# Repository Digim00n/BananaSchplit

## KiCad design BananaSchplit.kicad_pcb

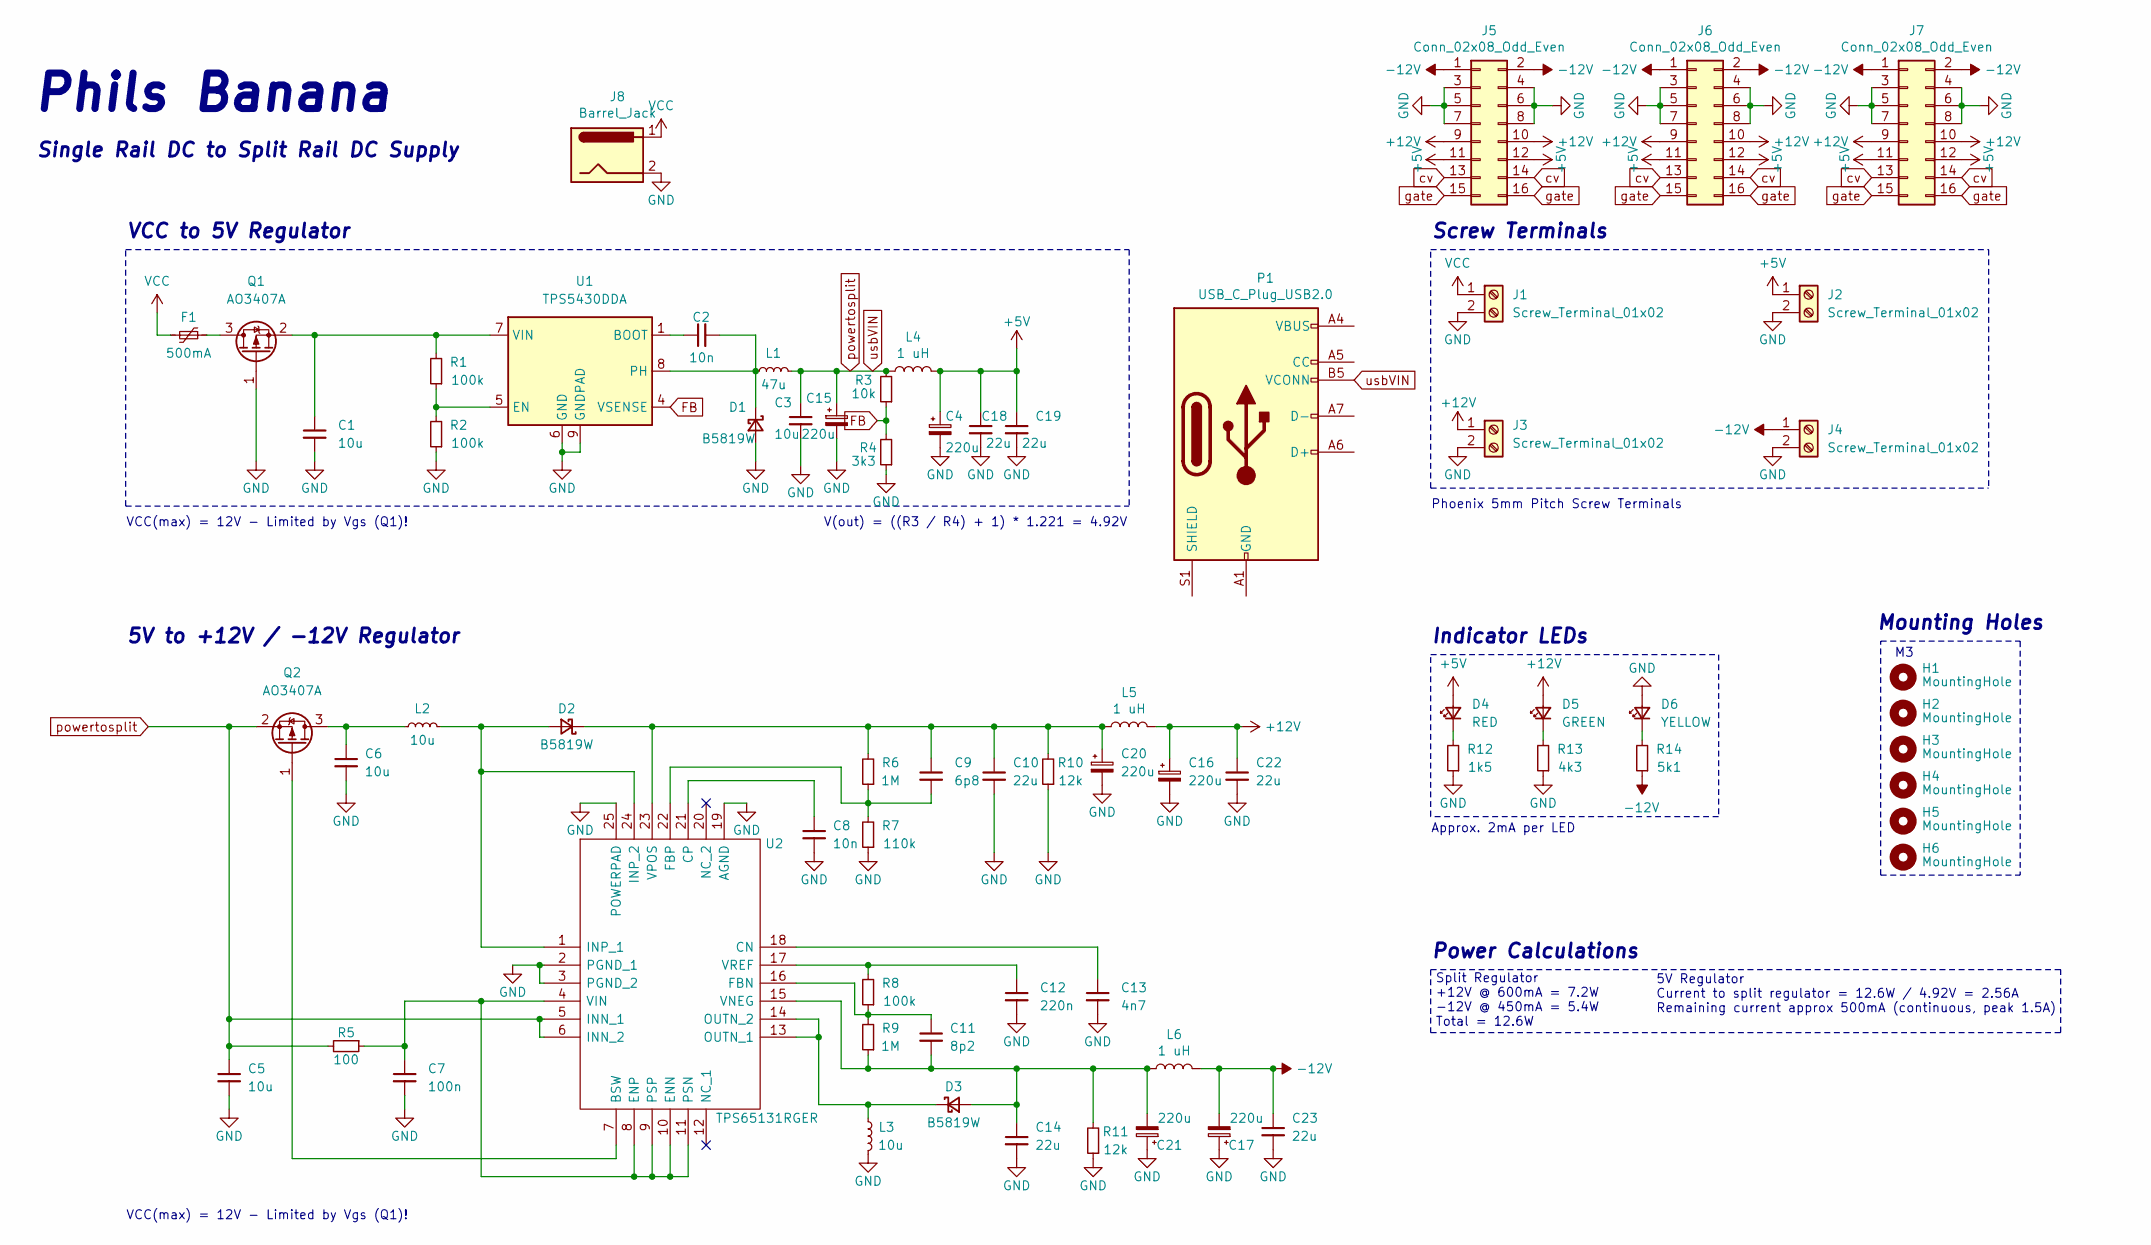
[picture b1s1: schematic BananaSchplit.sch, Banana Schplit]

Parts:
C1, C3, C5, C6: 10u; C_1206_3216Metric; LCSC Part # C13585
C2, C8: 10n; C_0603_1608Metric; LCSC Part # C57112
C4, C15, C16, C17, C20, C21: 220u; CP_Elec_6.3x7.7; LCSC Part # C127327
C7: 100n; C_0603_1608Metric; LCSC Part # C14663
C9: 6p8; C_0603_1608Metric; LCSC Part # C1679
C10, C14, C18, C19, C22, C23: 22u; C_0805_2012Metric; LCSC Part # C45783
C11: 8p2; C_0603_1608Metric; LCSC Part # C1685
C12: 220n; C_0603_1608Metric; LCSC Part # C21120
C13: 4n7; C_0603_1608Metric; LCSC Part # C53987
D1, D2, D3: B5819W; D_SOD-123; LCSC Part # C8598
D4: RED; LED_0805_2012Metric; LCSC Part # C84256
D5: GREEN; LED_0805_2012Metric; LCSC Part # C2297
D6: YELLOW; LED_0805_2012Metric; LCSC Part # C2296
F1: 500mA; Fuse_1812_4532Metric; LCSC Part # C151168
H1, H2, H3, H4, H5, H6: MountingHole; MountingHole_3.2mm_M3
J1, J2, J3, J4: Screw_Terminal_01x02; TerminalBlock_Phoenix_PT-1,5-2-5.0-H_1x02_P5.00mm_Horizontal
J5, J6, J7: Conn_02x08_Odd_Even; PinSocket_2x08_P2.54mm_Vertical
J8: Barrel_Jack; BarrelJack_Horizontal
L1: 47u; SWRB1204S; LCSC Part # C169398
L2, L3: 10u; L_Sunlord_MWSA0518_5.4x5.2mm; LCSC Part # C139506
L4, L5, L6: 1 uH; TYS60281R0N-10
P1: USB_C_Plug_USB2.0; USB_C_Receptacle_HRO_TYPE-C-31-M-12
Q1, Q2: AO3407A; SOT-23; LCSC Part # C347478
R1, R2, R8: 100k; R_0603_1608Metric; LCSC Part # C25803
R3: 10k; R_0603_1608Metric; LCSC Part # C25804
R4: 3k3; R_0603_1608Metric; LCSC Part # C22978
R5: 100; R_0603_1608Metric; LCSC Part # C22775
R6, R9: 1M; R_0603_1608Metric; LCSC Part # C22935
R7: 110k; R_0603_1608Metric; LCSC Part # C25805
R10, R11: 12k; R_0603_1608Metric; LCSC Part # C22790
R12: 1k5; R_0603_1608Metric; LCSC Part # C22843
R13: 4k3; R_0603_1608Metric; LCSC Part # C23159
R14: 5k1; R_0603_1608Metric; LCSC Part # C23186
U1: TPS5430DDA; TI_SO-PowerPAD-8_ThermalVias; LCSC Part # C9864
U2: TPS65131RGER; QFN-24-1EP_4x4mm_P0.5mm_EP2.6x2.6mm; Mouser2 Part Number 595-TPS65131RGET

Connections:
+5V: C4.1, C18.1, C19.1, D4.2 (A), J2.1, J5.11, J5.12, J6.11, J6.12, J7.11, J7.12, L4.2
+12V: C16.1, C22.1, D5.2 (A), J3.1, J5.9, J5.10, J6.9, J6.10, J7.9, J7.10, L5.2
-12V: C17.2, C23.1, J4.1, J5.1, J5.2, J6.1, J6.2, J7.1, J7.2, L6.2, R14.1
FB: R3.1, R4.2, U1.4 (VSENSE)
GND: C1.2, C3.2, C4.2, C5.2, C6.2, C7.2, C8.2, C10.2, C12.2, C13.2, C14.2, C15.2, C16.2, C17.1, C18.2, C19.2, C20.2, C21.1, C22.2, C23.2, D1.2 (A), D6.2 (A), J1.2, J2.2, J3.2, J4.2, J5.3, J5.4, J5.5, J5.6, J5.7, J5.8, J6.3, J6.4, J6.5, J6.6, J6.7, J6.8, J7.3, J7.4, J7.5, J7.6, J7.7, J7.8, J8.2, L3.2, Q1.1 (G), R2.1, R4.1, R7.1, R10.1, R11.1, R12.1, R13.1, U1.6 (GND), U1.9 (GNDPAD), U2.2 (PGND_1), U2.3 (PGND_2), U2.19 (AGND), U2.25 (POWERPAD)
unnamed: C1.1, Q1.2 (S), R1.2, U1.7 (VIN)
unnamed: C2.1, U1.1 (BOOT)
unnamed: C2.2, D1.1 (K), L1.1, U1.8 (PH)
unnamed: C6.1, L2.1, Q2.3 (D)
unnamed: C7.1, R5.1, U2.4 (VIN), U2.8 (ENP), U2.9 (PSP), U2.10 (ENN), U2.11 (PSN)
unnamed: C8.1, U2.21 (CP)
unnamed: C9.2, R6.1, R7.2, U2.22 (FBP)
unnamed: C9.1, C10.1, C20.1, D2.1 (K), L5.1, R6.2, R10.2, U2.23 (VPOS)
unnamed: C11.1, R8.1, R9.2, U2.16 (FBN)
unnamed: C11.2, C14.1, C21.2, D3.2 (A), L6.1, R9.1, R11.2, U2.15 (VNEG)
unnamed: C12.1, R8.2, U2.17 (VREF)
unnamed: C13.1, U2.18 (CN)
unnamed: D2.2 (A), L2.2, U2.1 (INP_1), U2.24 (INP_2)
unnamed: D3.1 (K), L3.1, U2.13 (OUTN_1), U2.14 (OUTN_2)
unnamed: D4.1 (K), R12.2
unnamed: D5.1 (K), R13.2
unnamed: D6.1 (K), R14.2
unnamed: F1.1, Q1.3 (D)
unnamed: P1.A1 (GND), P1.A12 (GND), P1.B1 (GND), P1.B12 (GND)
unnamed: P1.A4 (VBUS), P1.A9 (VBUS), P1.B4 (VBUS), P1.B9 (VBUS)
unnamed: Q2.1 (G), U2.7 (BSW)
unnamed: R1.1, R2.2, U1.5 (EN)
VCC: F1.2, J1.1, J8.1
cv: J5.13, J5.14, J6.13, J6.14, J7.13, J7.14
gate: J5.15, J5.16, J6.15, J6.16, J7.15, J7.16
powertosplit: C3.1, C5.1, C15.1, L1.2, L4.1, P1.B5 (VCONN), Q2.2 (S), R3.2, R5.2, U2.5 (INN_1), U2.6 (INN_2)

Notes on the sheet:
VCC to 5V Regulator
5V to +12V / -12V Regulator
Screw Terminals
Indicator LEDs
Mounting Holes
Phils Banana
Single Rail DC to Split Rail DC Supply
VCC(max) = 12V - Limited by Vgs (Q1)!
V(out) = ((R3 / R4) + 1) * 1.221 = 4.92V
Phoenix 5mm Pitch Screw Terminals
Approx. 2mA per LED
Split Regulator +12V @ 600mA = 7.2W -12V @ 450mA = 5.4W Total = 12.6W
5V Regulator Current to split regulator = 12.6W / 4.92V = 2.56A Remaining current approx 500mA (continuous, peak 1.5A)
Power Calculations

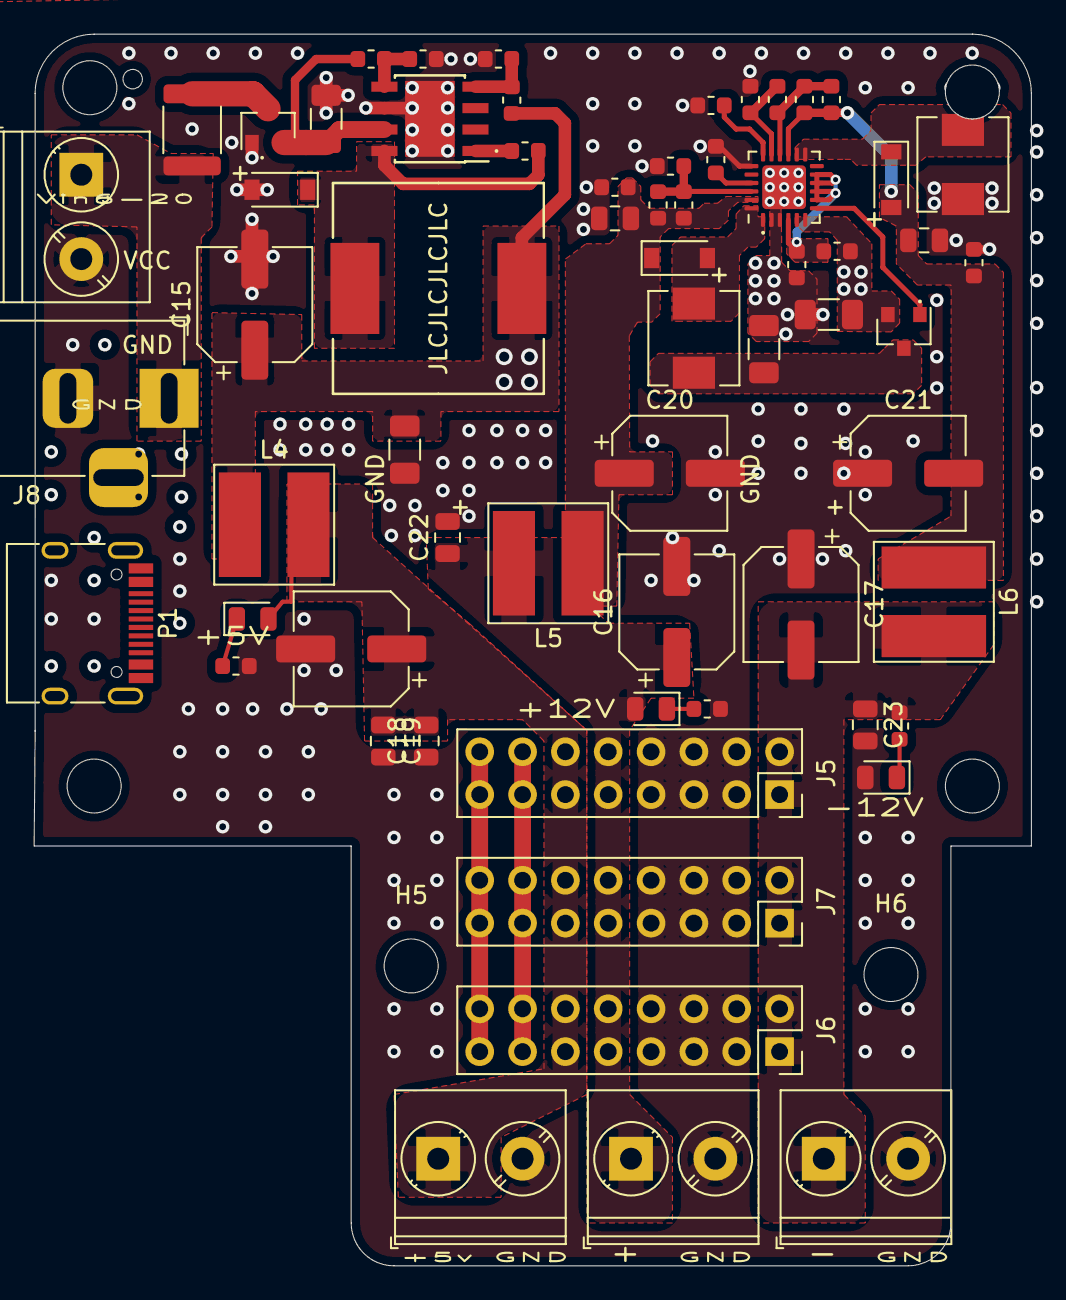
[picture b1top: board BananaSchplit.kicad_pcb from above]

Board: 2 copper layers, 59.1 x 73.0 mm, 69 parts (0 on the bottom side), 31 nets.

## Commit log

2021-11-08 filtering + euroheaders
    added more filtering/capacitance.
    changed layout, added eurroack power headers and more inputs
